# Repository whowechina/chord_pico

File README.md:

# Chord Pico - Polaris Chord Mini Controller
[点这里可以切换到中文版](README_CN.md)

Features:
* World's first Polaris Chord controller.
* Two versions available: Chord Pico for 15.6 to 21 inches monitors, Chord Pico+ for 21.5 inches and above.
* Almost all parts are 3D printed.
* Hall effect keys with configurable travel distance.
* RGB key lights with HID light support.
* Fader sensors are arcade accurate.
* All open source.

Thanks to the many generous individuals and companies who made their tools or materials free or open source (KiCad, OnShape, InkScape, Raspberry things, JLCPCB and Jiepei).

Special thanks to community projects and developers. And also these projects:
* RP_Silicon_KiCad: https://github.com/HeadBoffin/RP_Silicon_KiCad
* Type-C: https://github.com/ai03-2725/Type-C.pretty

## About the License
It's CC-NC. So DIY for yourself and your friends, don't make money from it. Plagiarism, especially without crediting the original author, is not acceptable. Please note that pooling orders and group buying for raw materials are acceptable. Selling off any leftover components without profit is also acceptable.

If you're interested in buying from me, or in commercial use, please contact me (Discord, QQ group, Goofish).
* My Discord Invitation: https://discord.gg/M8f2PPQFEA
* QQ Group: 854535476
* Goofish: whowe12345

## My Other Projects
You can check out my other cool projects.

* Popn Pico: https://github.com/whowechina/popn_pico
* IIDX Pico: https://github.com/whowechina/iidx_pico
* Chu Pico: https://github.com/whowechina/chu_pico
* Mai Pico: https://github.com/whowechina/mai_pico
* Diva Pico: https://github.com/whowechina/diva_pico
* AIC Pico: https://github.com/whowechina/aic_pico
* Groove Pico: https://github.com/whowechina/groove_pico
* Geki Pico: https://github.com/whowechina/geki_pico
* Musec Pico: https://github.com/whowechina/musec_pico
* Ju Pico: https://github.com/whowechina/ju_pico
* Bishi Pico: https://github.com/whowechina/bishi_pico
* Nos Pico: https://github.com/whowechina/nos_pico
* Voltex Pico: https://github.com/whowechina/voltex_pico
* Chord Pico: https://github.com/whowechina/chord_pico
* Dance Pico: https://github.com/whowechina/dance_pico
* Arcade Pico: https://github.com/whowechina/arcade_pico

## **Disclaimer** ##
I made this project in my personal time without any sponsorship. I will continue to improve the project. I have done my best to ensure that everything is accurate and functional, but there's always a chance that mistakes may occur. I cannot be held responsible for any loss of time or money that may result from using this open source project. Thank you for your understanding.

## HOW TO BUILD
### PCB and Components
* Go to JLCPCB or any PCB vendor you like, and place an order with the gerber zip files (latest `Production\PCB\chord_pico_xxx.zip` for Chord Pico or `Production\PCB\chord_plus_xxx.zip` for Chord Pico+), regular FR-4 board, black color, **1.6mm** thickness.

* 1x Raspberry Pi Pico or pin-to-pin compatible clones, those with type-C port are strongly recommended.  
  https://www.raspberrypi.com/products/raspberry-pi-pico
* 1x USB Type-C socket (918-418K2023S40001 or KH-TYPE-C-16P)
* 1x ADG706BRUZ (28-TSSOP) 16 to 1 analog multiplexer (U2).  
  https://www.analog.com/en/products/adg706.html
* 12x SS49E (SOT23) linear Hall effect sensors (H1 to H12).
* 10x ITR1502SR40A/TR8 reflective photosensors (IR1 to IR10).  
  https://www.lcsc.com/product-detail/C183793.html
* 1x TPS7A2042PDBVR (4.2V) or LP5907MFX-4.5 (4.5V) LDO (SOT23-5), (U7).  
  https://www.ti.com/product/TPS7A20/part-details/TPS7A2042PDBVR
* 1x LM4040 3.0V Shunt Voltage Reference, in SOT23-3 (U6). There're many models; make sure it's 3.0V and in an SOT23-3 package.
* Optional: 1x Zener diode 3.0 or 3.3V, in SOD-123F (Z1). It's for extra protection for the GPIO, but the risk is very low.
* 42x WS2812B-3528 RGB LEDs (D1 to D42). D1 to D12 and D35 to D38 are mandatory; others are for better lighting.
* 20x to 30x 0603 0.1uF (0.1~1uF all fine) capacitors. CC1 to CC3 are mandatory; others are optional (see notes below).
* 3x 0603 5.1kohm resistors, 2 for USB (R1, R2) and 1 for signal divider (R4).
* 1x 0603 2kohm resistor for signal divider (R3).
* 10x 0603 200ohm resistors as photosensor current limiters (R5, R7, R9, ... R23).
* 10x 0603 22kohm resistors as photosensor pull-downs (R6, R8, R10, ... R24) (see notes below).
* 2x ALPS SKHHLWA010 6\*6\*7mm or compatible tactile switches (SW1, SW2).  
  https://tech.alpsalpine.com/e/products/detail/SKHHLWA010/

* This is what the Chord Pico board looks like after soldering. Chord Pico+ looks a little different, but the components are the same.  

### Notes
1. Be careful of 2 USB pins (holes) for the Pi Pico. It's a common oversight to either forget to solder them or to leave air bubbles during the process. To avoid this, solder slowly from only one side of the hole.  
   
2. There are many capacitors for decoupling. You don't need to solder them all. You can solder only some of them; just distribute them evenly.
3. If you find a photosensor oversensitive, you need to use a lower resistance, e.g. 15kohm; otherwise, if it's not sensitive enough, you can use a higher resistance, e.g. 27kohm or 33kohm. Also you can measure the idle voltage across the pull-down resistor (R6, R8, ...) when nothing is above the photosensor. Higher resistance gives higher idle voltage, 0.1v to 0.2v is a good range.

### Test the PCB
* You can test the PCB now, put the firmware in.
* Most likely all key LEDs will light up and flash.
* Left fader LEDs will light up green, right fader LEDs will light up pink.
* Chord Pico should be recognized as a USB HID device. Here's the test page.  
  https://whowechina.github.io/iidx_pico/Tools/gamepad_test.html
* Use a terminal tool to connect to Chord Pico's command line interface.
  https://whowechina.github.io/iidx_pico/Tools/cli_tool.html
* Use `debug hall` to toggle hall effect sensor debug mode. When it's on, you can see the real-time sensor values. Use a small magnet to test them one by one. The value should change significantly when a magnet is close to the corresponding sensor. If you notice strange values, check the soldering of the multiplexer and the corresponding hall effect sensor.
* Use `debug fader` to toggle fader sensor debug mode. When it's on, you can see real-time fader sensor status. You can use a white object (e.g. paper), waving it 5mm above the sensor to see the response.
* Only when PCB is fully functional, you can proceed to the assembly.

### 3D Printing
#### Printing parameters  
* PLA or PETG.
* Layer height: 0.2mm
* Support: No, unless explicitly mentioned.
* Files are always in millimeter units, not inches.
* Parts can fit on a 256mm\*256mm bed, you may need to rotate them to fit.

#### Parts
* All files are in `Production\3DPrint` folder.
* Use files with `+` for Chord Pico+, including `Chord Pico+`, `Key+` and `Fader+`.
* Keys: `Key Combo - All Keys`, clear or transparent.
* Rear Base: `Chord Pico - Rear.stl`, black. Enable support and use support material to have better screw holes.
* Front Base: `Chord Pico - Front.stl`, black. Enable support and use support material to have better screw holes. Note that for Chord Pico+ version, the front base is split into two parts: `Chord Pico+ - Left` and `Chord Pico+ - Right`.
* Panel: `Chord Pico - Panel Combo.3mf`, a multi-color system is highly recommended, make the "Panel White Layer" white, others black. Print upside down.
* Brim (Key Stopper): `Chord Pico - Brim Insert.stl` is recommended, but if you can't use heat-set inserts, use `Chord Pico - Brim.stl` instead (see notes below). Use black filament. Print upside down. Note that for Chord Pico+ version, the brim is split into two parts: `Chord Pico+ - BrimLeft` and `Chord Pico+ - BrimRight`, both use heat-set inserts.
* Fader parts for Chord Pico only:
  * 2x Fader Slider: `Slider PTFE.stl` is recommended, but if you can't find proper PTFE tube, use `Slider Thruhole.stl` instead (see notes below). Must be white.  
  * 2x Fader Seal: `Slider Seal.stl`, white.
  * 4x Rail Fixers: `Chord Pico - Rail Fixer.stl`, color doesn't matter.
  * 2x Fader Knobs: `Fader - Knob.stl`, one in green, one in red.
* Fader parts for Chord Pico+ only:
  * 2x Fader seats: `Fader+ - Seat`, black, embed heat-set inserts after printing.
  * 2x Fader curtains: `Fader+ - Curtain`, black.
  * 2x Reflectors: `Fader+ - Reflector`, **MUST** be white.
  * 2x Fader Knobs: `Fader+ - Knob+.stl`, one in green, one in red.

#### Notes
1. For the Brim (Key Stopper), heat-set inserts are recommended; they provide a better solution than self-tapping threads. But if you can't find them or don't have the tools, you can use self-tapping version instead, just be careful when screwing, do it slowly and don't overtighten.
2. For the Fader Slider, a PTFE tube is recommended for smoother feel. If you can't find proper PTFE tube, you can use the through-hole version.

### Assembly
#### Other components needed
* 13x M3\*6mm screws for the PCB to the front and rear base. For Chord Pico+ version, 18x are needed.
* 7x M3\*10mm screws for the panel to the rear base.
* 7x M2\*10mm screws for the front base to the brim. For Chord Pico+ version, 9x are needed.

* Fader components for Chord Pico only:
  * 4x 2mm\*70mm (diameter\*length) steel shafts for the fader rails.
  * Some 2.2mm\*4mm or 2.3mm\*4mm (inner diameter\*outer diameter) PTFE tubes.
  * 4x 0.3mm\*5mm\*15mm (wire diameter\*outer diameter\*length) close-wound tension springs, for the faders.
  * 24x M2\*7mm screws for the slider.
  * 2x M2\*16~18mm screws for the fader knobs.

* Fader components for Chord Pico+ only:
  * 2x MGN7 100mm linear rails.
  * 2x MGN7C sliders.
  * 4x 0.4mm\*5mm\*30mm (wire diameter\*outer diameter\*length) close-wound tension springs, for the faders.
  * 8x M2\*8mm screws for securing the rails to the base.
  * 8x M2 washers, for the screws that secure the tension springs. Metal or plastic both work.
  * 4x M2\*4mm screws for securing the tension springs on the slider side.
  * 4x M2\*6mm screws for securing the tension springs on the spring posts at both ends of the rails.
  * 8x M2\*8mm screws for securing the curtains and fader seats to the sliders.
  * 2x M2.5\*18mm screws for securing the fader knobs to the fader seats.
  
* 7x M2\*3mm\*3mm (outer diameter\*height) heat-set inserts for Chord Pico brim. For Chord Pico+, 9x are needed.
* 7x M3\*4mm\*4mm (outer diameter\*height) heat-set inserts for Chord Pico panel. For Chord Pico+, 9x are needed.
* Only for Chord Pico+: 2x M2.5\*3.5mm\*6mm (outer diameter\*height) heat-set inserts for the fader seats.

* 1x 2mm diameter steel shaft. 250mm length for Chord Pico, 340mm length for Chord Pico+.

* 12x 0.4\*5\*10\*6N (0.4mm wire diameter, 5mm outer diameter, 10mm free length, 6 turns) springs. For Chord Pico+, 24x are needed.
* 12x 3mm\*2mm (diameter\*height) axial magnetized cylinder magnets.
* Some white silicone adhesive, such as K-704 silicone industrial adhesive.
* Some damping grease, low viscosity, such as Runsai's type-2.

* Some 0.5~0.8mm thick self-adhesive foam tape (Poron or EVA) for damping.

* Some 10mm\*2mm or 10mm\*2mm (diameter\*height) black silicone self-adhesive anti-slip pads.

#### Steps
Please note that the design may change in the future, but the assembly steps will remain the same. So ignore minor differences in some details.

1. Please install heat-set inserts into the parts that require them.

2. Use the M3\*6mm screws to fix the PCB to the front and rear base part. Note that for Chord Pico+ version, the base is assembled from three parts and needs more screws.  

3. Insert the magnets into the slots at the front of the keys and secure them with adhesive (such as white RTV 704 silicone glue).

4. Install the keys. Use the steel shaft to go through all keys, and then embed the steel shaft into the hinge sockets in the rear base.  

5. Fader assembly for Chord Pico only:
   1. Cut some pieces of PTFE tube and embed them into the slider. They provide smoothness while sliding the faders. If you do not use PTFE tube, please use the through-hole slider and skip this step.  

   2. Insert the close-wound tension springs into the slider, then use M2 screws to secure the slider seal to the slider.  

   3. While the steel shafts are inserted, put the slider combo into the rear base. Then hook the springs to the base and finally use M2 screws and the rail fixers to secure the slider combo. You can apply a little bit of damping grease to the steel shafts to make the slider less bouncy.  
       
6. Fader assembly for Chord Pico+ only:
   1. Secure the two linear rails to the rear base using M2 screws.  
      
   2. Insert the reflectors into the fader seats, paying attention to their orientation.  
      
   3. Install the springs onto the fader seats using M2 screws and washers. Note that the screws for the fixed side and the moving side are different, and don’t overtighten them. The seats are floating on the sliders for now.  
      
   4. Place the curtains onto the sliders, push them firmly against the sliders, then use M2 screws to secure them.  

7. Install the springs for the keys. Chord Pico+ has two springs per key.  

8. Now do another test. Power on and calibrate the keys. Keys and faders should work properly. If everything is fine, proceed to the next step.

9. Optional but highly recommended: use some foam tape to dampen the key noise. You need to stick the foam tape to the PCB (right below the Hall sensors) and the key stopper (brim) part. They reduce the key down and key up noise significantly.  

10. Chord Pico only. If the area of the panel above the sensors is printed with white material, use a black marker to color it. This helps reduce the risk of sensor interference.  

11. Chord Pico+ only. Apply thin PTFE/UHMW tape to the inner top surface of the panel so the slider curtains don’t squeak when sliding.  

12. Put the panel onto the base. The two auxiliary switches can interfere with the panel during installation, so move the right slider to the left and gently flex the panel to snap it into place. Then use the M3\*10mm screws to secure the panel to the base.  

13. Perform another test. Power on and calibrate. Make sure everything still works.

14. Install the knobs. The left is green and the right one is red. Secure them using the long screws (M2 for Chord Pico, M2.5 for Chord Pico+).

15. Install the brim (key stopper) part. If you use heat-set inserts, use the proper tools to install them into the brim first. Use M2\*10mm screws to secure the brim to the front base.  

16. Attach the anti-slip pads to the bottom of the controller.

17. Power on and recalibrate the keys.

18. Enjoy!  

### Firmware
* UF2 file is in `Production\Firmware` folder.
* For the new build, hold the BOOTSEL button while connecting the USB to a PC, a disk named "RPI-RP2" will appear. Drag the UF2 firmware binary file into it. Note that there is a small hole on the bottom side of the controller, aligned with the BOOTSEL button.
* If it's already running the firmware, you can either use `update` in the command line or hold down the two auxiliary switches while connecting to USB to enter update mode.
* To access the command line, you can use this Web Serial Terminal to connect to the controller's command line port. (Note: "?" is for help)  
  https://whowechina.github.io/iidx_pico/Tools/cli_tool.html

### Usage
* Just plug and play.
* Keys are mapped to HID buttons.
* Faders are mapped to the HID axes X and Y.
* Use the `calibrate` command to calibrate the Hall effect keys.
* Use the `trigger` command to set the trigger and reset distances.

## CAD Source File
I'm using OnShape free subscription. It's powerful, but it can't archive original designs locally, so I can only share the link here. STL/DXF/DWG files are exported from this online document.  
  https://cad.onshape.com/documents/6bb6f9e65a79e122747d4a2d/w/1074c535f59b2616ddc9d820/e/61a1d98d42199565d2d1adba

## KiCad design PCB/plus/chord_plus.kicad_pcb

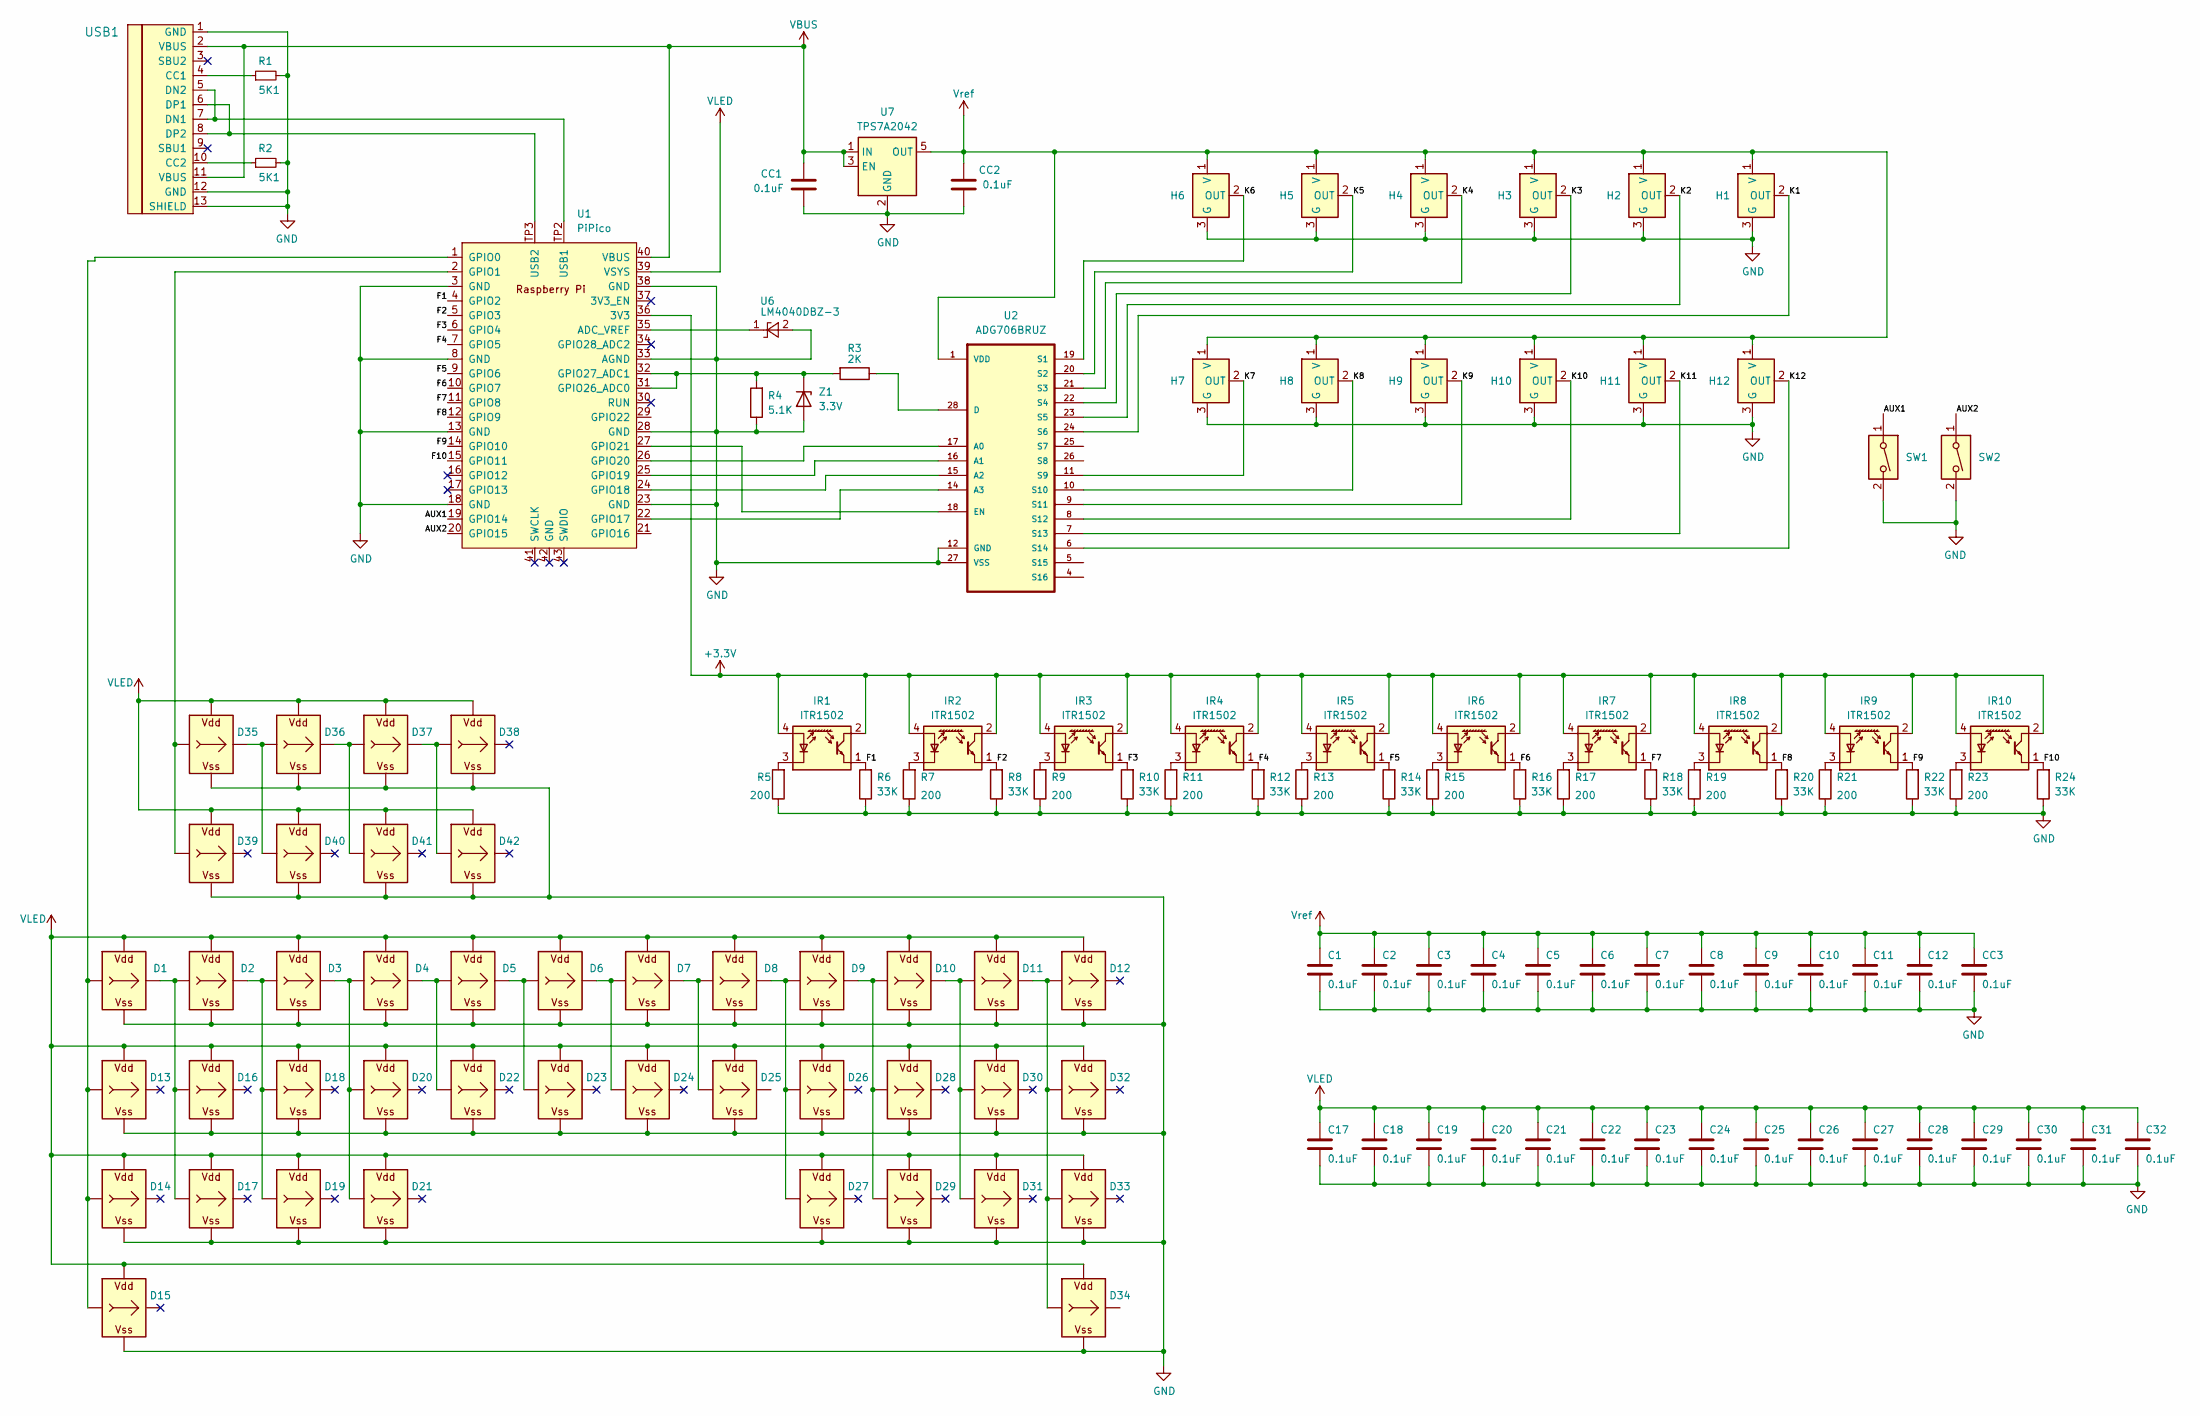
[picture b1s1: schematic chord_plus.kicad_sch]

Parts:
C1, C2, C3, C4, C5, C6, C7, C8, C9, C10, C11, C12, C17, C18, C19, C20, C21, C22, C23, C24, C25, C26, C27, C28, C29, C30, C31, C32: 0.1uF; C_0603_1608Metric_Pad1.08x0.95mm_HandSolder
CC1, CC2, CC3: 0.1uF; C_0603_1608Metric_Pad1.08x0.95mm_HandSolder
D1, D2, D3, D4, D5, D6, D7, D8, D9, D10, D11, D12, D13, D14, D15, D16, D17, D18, D19, D20, D21, D22, D23, D24, D25, D26, D27, D28, D29, D30, D31, D32, D33, D34, D35, D36, D37, D38, D39, D40, D41, D42: WS2812B_Unified; WS2812B-2835
H1, H2, H3, H4, H5, H6, H7, H8, H9, H10, H11, H12: SS49E_SOT23; SOT-23-FAT
IR1, IR2, IR3, IR4, IR5, IR6, IR7, IR8, IR9, IR10: ITR1502
R1, R2: 5K1; R_0603_1608Metric_Pad0.98x0.95mm_HandSolder; LCSC C23186
R3: 2K; R_0603_1608Metric_Pad0.98x0.95mm_HandSolder
R4: 5.1K; R_0603_1608Metric_Pad0.98x0.95mm_HandSolder
R5, R7, R9, R11, R13, R15, R17, R19, R21, R23: 200; R_0603_1608Metric_Pad0.98x0.95mm_HandSolder
R6, R8, R10, R12, R14, R16, R18, R20, R22, R24: 33K; R_0603_1608Metric_Pad0.98x0.95mm_HandSolder
SW1, SW2: SW_DIP_x01; Omron_B3F-315x_Angled
U1: PiPico; RPi_Pico_SMD_Pins
U2: ADG706BRUZ; TSSOP-28_4.4x9.7mm_P0.65mm
U6: LM4040DBZ-3; SOT-23-FAT
U7: TPS7A2042; SOT-23-5
USB1: U262-161N-4BVC11; HRO-TYPE-C-31-M-12-Assembly; LCSC C319148
Z1: 3.3V; D_SOD-123F

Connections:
+3.3V: IR1.2, IR1.4 (A), IR2.2, IR2.4 (A), IR3.2, IR3.4 (A), IR4.2, IR4.4 (A), IR5.2, IR5.4 (A), IR6.2, IR6.4 (A), IR7.2, IR7.4 (A), IR8.2, IR8.4 (A), IR9.2, IR9.4 (A), IR10.2, IR10.4 (A), U1.36 (3V3)
/AUX1: SW1.1, U1.19 (GPIO14)
/AUX2: SW2.1, U1.20 (GPIO15)
/F1: IR1.1, R6.2, U1.4 (GPIO2)
/F2: IR2.1, R8.2, U1.5 (GPIO3)
/F3: IR3.1, R10.2, U1.6 (GPIO4)
/F4: IR4.1, R12.2, U1.7 (GPIO5)
/F5: IR5.1, R14.2, U1.9 (GPIO6)
/F6: IR6.1, R16.2, U1.10 (GPIO7)
/F7: IR7.1, R18.2, U1.11 (GPIO8)
/F8: IR8.1, R20.2, U1.12 (GPIO9)
/F9: IR9.1, R22.2, U1.14 (GPIO10)
/F10: IR10.1, R24.2, U1.15 (GPIO11)
/K1: H1.2 (OUT), U2.24 (S6)
/K2: H2.2 (OUT), U2.23 (S5)
/K3: H3.2 (OUT), U2.22 (S4)
/K4: H4.2 (OUT), U2.21 (S3)
/K5: H5.2 (OUT), U2.20 (S2)
/K6: H6.2 (OUT), U2.19 (S1)
/K7: H7.2 (OUT), U2.11 (S9)
/K8: H8.2 (OUT), U2.10 (S10)
/K9: H9.2 (OUT), U2.9 (S11)
/K10: H10.2 (OUT), U2.8 (S12)
/K11: H11.2 (OUT), U2.7 (S13)
/K12: H12.2 (OUT), U2.6 (S14)
GND: C1.2, C2.2, C3.2, C4.2, C5.2, C6.2, C7.2, C8.2, C9.2, C10.2, C11.2, C12.2, C17.2, C18.2, C19.2, C20.2, C21.2, C22.2, C23.2, C24.2, C25.2, C26.2, C27.2, C28.2, C29.2, C30.2, C31.2, C32.2, CC1.2, CC2.2, CC3.2, D1.G (VSS), D2.G (VSS), D3.G (VSS), D4.G (VSS), D5.G (VSS), D6.G (VSS), D7.G (VSS), D8.G (VSS), D9.G (VSS), D10.G (VSS), D11.G (VSS), D12.G (VSS), D13.G (VSS), D14.G (VSS), D15.G (VSS), D16.G (VSS), D17.G (VSS), D18.G (VSS), D19.G (VSS), D20.G (VSS), D21.G (VSS), D22.G (VSS), D23.G (VSS), D24.G (VSS), D25.G (VSS), D26.G (VSS), D27.G (VSS), D28.G (VSS), D29.G (VSS), D30.G (VSS), D31.G (VSS), D32.G (VSS), D33.G (VSS), D34.G (VSS), D35.G (VSS), D36.G (VSS), D37.G (VSS), D38.G (VSS), D39.G (VSS), D40.G (VSS), D41.G (VSS), D42.G (VSS), H1.3 (G), H2.3 (G), H3.3 (G), H4.3 (G), H5.3 (G), H6.3 (G), H7.3 (G), H8.3 (G), H9.3 (G), H10.3 (G), H11.3 (G), H12.3 (G), R1.2, R2.2, R4.1, R5.1, R6.1, R7.1, R8.1, R9.1, R10.1, R11.1, R12.1, R13.1, R14.1, R15.1, R16.1, R17.1, R18.1, R19.1, R20.1, R21.1, R22.1, R23.1, R24.1, SW1.2, SW2.2, U1.3 (GND), U1.8 (GND), U1.13 (GND), U1.18 (GND), U1.23 (GND), U1.28 (GND), U1.33 (AGND), U1.38 (GND), U2.12 (GND), U2.27 (VSS), U6.2 (A), U7.2 (GND), USB1.1 (GND), USB1.12 (GND), USB1.13 (SHIELD), Z1.2 (A)
unnamed: D1.I (In), D13.I (In), D14.I (In), D15.I (In), U1.1 (GPIO0)
unnamed: D1.O (Out), D2.I (In), D16.I (In), D17.I (In)
unnamed: D9.O (Out), D10.I (In), D28.I (In), D29.I (In)
unnamed: D10.O (Out), D11.I (In), D30.I (In), D31.I (In)
unnamed: D11.O (Out), D12.I (In), D32.I (In), D33.I (In), D34.I (In)
unnamed: D2.O (Out), D3.I (In), D18.I (In), D19.I (In)
unnamed: D3.O (Out), D4.I (In), D20.I (In), D21.I (In)
unnamed: D4.O (Out), D5.I (In), D22.I (In)
unnamed: D5.O (Out), D6.I (In), D23.I (In)
unnamed: D6.O (Out), D7.I (In), D24.I (In)
unnamed: D7.O (Out), D8.I (In), D25.I (In)
unnamed: D8.O (Out), D9.I (In), D26.I (In), D27.I (In)
unnamed: D35.I (In), D39.I (In), U1.2 (GPIO1)
unnamed: D35.O (Out), D36.I (In), D40.I (In)
unnamed: D36.O (Out), D37.I (In), D41.I (In)
unnamed: D37.O (Out), D38.I (In), D42.I (In)
unnamed: IR1.3 (K), R5.2
unnamed: IR2.3 (K), R7.2
unnamed: IR3.3 (K), R9.2
unnamed: IR4.3 (K), R11.2
unnamed: IR5.3 (K), R13.2
unnamed: IR6.3 (K), R15.2
unnamed: IR7.3 (K), R17.2
unnamed: IR8.3 (K), R19.2
unnamed: IR9.3 (K), R21.2
unnamed: IR10.3 (K), R23.2
unnamed: U1.35 (ADC_VREF), U6.1 (K)
unnamed: U1.22 (GPIO17), U2.14 (A3)
unnamed: U1.24 (GPIO18), U2.15 (A2)
unnamed: U1.25 (GPIO19), U2.16 (A1)
unnamed: U1.26 (GPIO20), U2.17 (A0)
unnamed: U1.27 (GPIO21), U2.18 (EN)
unnamed: R3.2, R4.2, U1.31 (GPIO26_ADC0), U1.32 (GPIO27_ADC1), Z1.1 (K)
unnamed: U1.TP2 (USB1), USB1.5 (DN2), USB1.7 (DN1)
unnamed: U1.TP3 (USB2), USB1.6 (DP1), USB1.8 (DP2)
unnamed: R3.1, U2.28 (D)
unnamed: R1.1, USB1.4 (CC1)
unnamed: R2.1, USB1.10 (CC2)
VBUS: CC1.1, U1.40 (VBUS), U7.1 (IN), U7.3 (EN), USB1.2 (VBUS), USB1.11 (VBUS)
VLED: C17.1, C18.1, C19.1, C20.1, C21.1, C22.1, C23.1, C24.1, C25.1, C26.1, C27.1, C28.1, C29.1, C30.1, C31.1, C32.1, D1.V (VDD), D2.V (VDD), D3.V (VDD), D4.V (VDD), D5.V (VDD), D6.V (VDD), D7.V (VDD), D8.V (VDD), D9.V (VDD), D10.V (VDD), D11.V (VDD), D12.V (VDD), D13.V (VDD), D14.V (VDD), D15.V (VDD), D16.V (VDD), D17.V (VDD), D18.V (VDD), D19.V (VDD), D20.V (VDD), D21.V (VDD), D22.V (VDD), D23.V (VDD), D24.V (VDD), D25.V (VDD), D26.V (VDD), D27.V (VDD), D28.V (VDD), D29.V (VDD), D30.V (VDD), D31.V (VDD), D32.V (VDD), D33.V (VDD), D34.V (VDD), D35.V (VDD), D36.V (VDD), D37.V (VDD), D38.V (VDD), D39.V (VDD), D40.V (VDD), D41.V (VDD), D42.V (VDD), U1.39 (VSYS)
Vref: C1.1, C2.1, C3.1, C4.1, C5.1, C6.1, C7.1, C8.1, C9.1, C10.1, C11.1, C12.1, CC2.1, CC3.1, H1.1 (V), H2.1 (V), H3.1 (V), H4.1 (V), H5.1 (V), H6.1 (V), H7.1 (V), H8.1 (V), H9.1 (V), H10.1 (V), H11.1 (V), H12.1 (V), U2.1 (VDD), U7.5 (OUT)

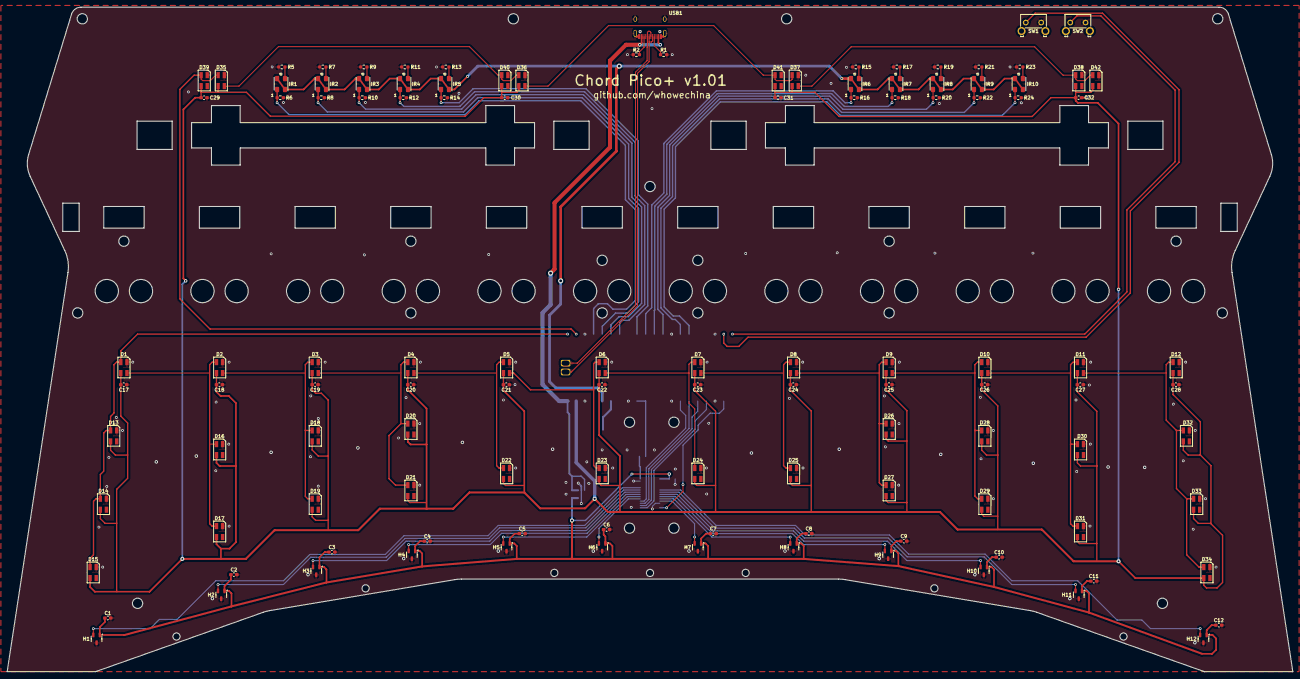
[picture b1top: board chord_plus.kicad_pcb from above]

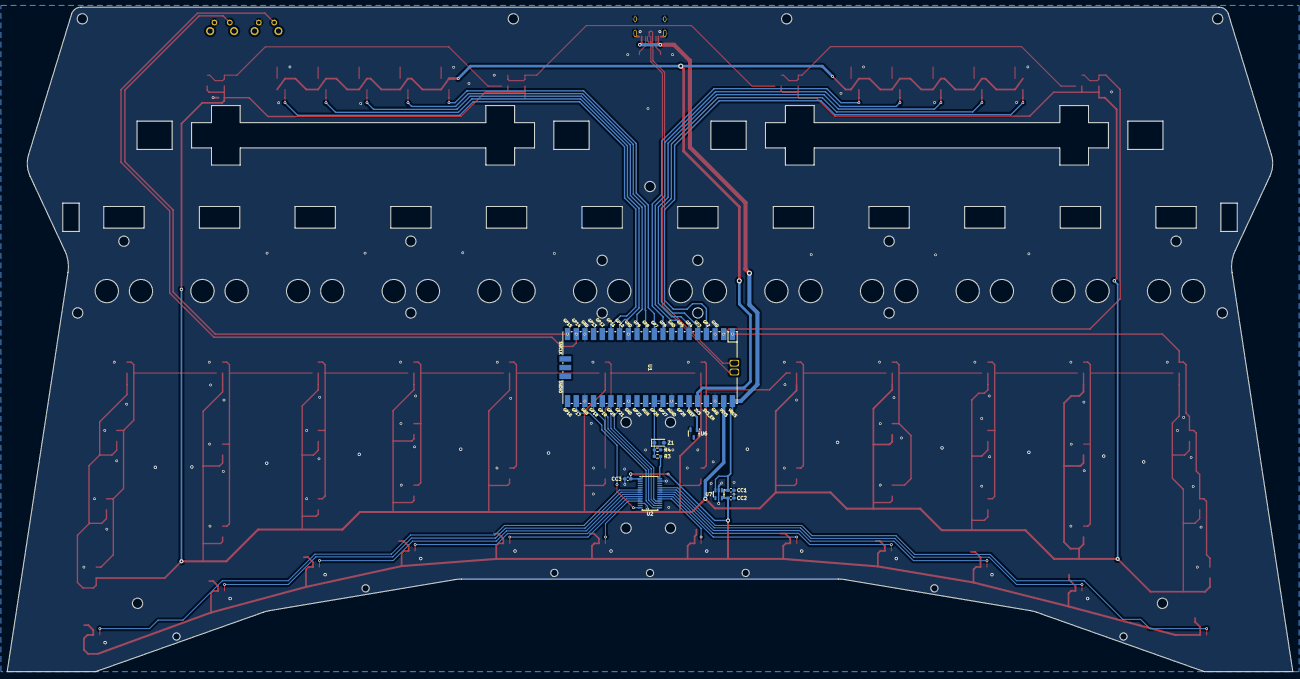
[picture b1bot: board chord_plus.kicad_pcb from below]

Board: 2 copper layers, 376.3 x 194.5 mm, 127 parts (10 on the bottom side), 67 nets.

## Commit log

2025-06-18 Reference materials
2025-06-20 PCB early layout
2025-06-20 PCB progress 60%
2025-06-24 PCB v1.0
2025-06-29 Firmware barely works
2025-07-04 PCB v1.11
2025-07-04 Firmware works
2025-08-22 Remove useless fader command
2025-08-22 GPIO pull up and down defs
2025-08-22 Defaults for trigger
2025-09-17 PCB v1.2 (correct values and signature)
2025-09-20 3D print files
2025-09-20 README in English
2025-09-20 Fix the missing heat-set inserts part
2025-09-20 Fix ADG706 footprint description
2025-09-20 Print orientation clarification
2025-09-20 A little wider fader slots
2025-09-20 README in Chinese
2025-09-21 Update README.md
    Correct one typo and wrong Zener Diode position name from D1 to Z1
2025-09-21 Update README_CN.md
    Same
2025-09-27 Minor format fix
2025-09-29 Comment on "too-sensitive" fader sensor
2025-10-05 Resistor and screw spec optimization
2025-10-06 Better resistor value
2025-10-09 Make zener diode optional
2025-10-12 A Readme fix (D1 -> Z1)
2025-10-16 Move sensor readings to the end of the HID button map
2025-10-16 Periodic HID report as well as edge-trigger
2025-10-18 Separate fader light from HID lights
2025-11-26 Chord Pico+ PCB v1.0
2025-12-02 Fix fader debug display
2025-12-14 PCB optimization, VBUS for LDO
2026-01-07 Chord Pico+ files
2026-02-02 Pico+ doc update (partial)
2026-02-02 Doc update for Pico+
2026-02-02 Minor doc update
2026-03-05 Chord Pico Panel improvement
2026-03-05 Option to include raw fader in HID
2026-03-11 Better knobs print without support
2026-03-11 Doc reference update
